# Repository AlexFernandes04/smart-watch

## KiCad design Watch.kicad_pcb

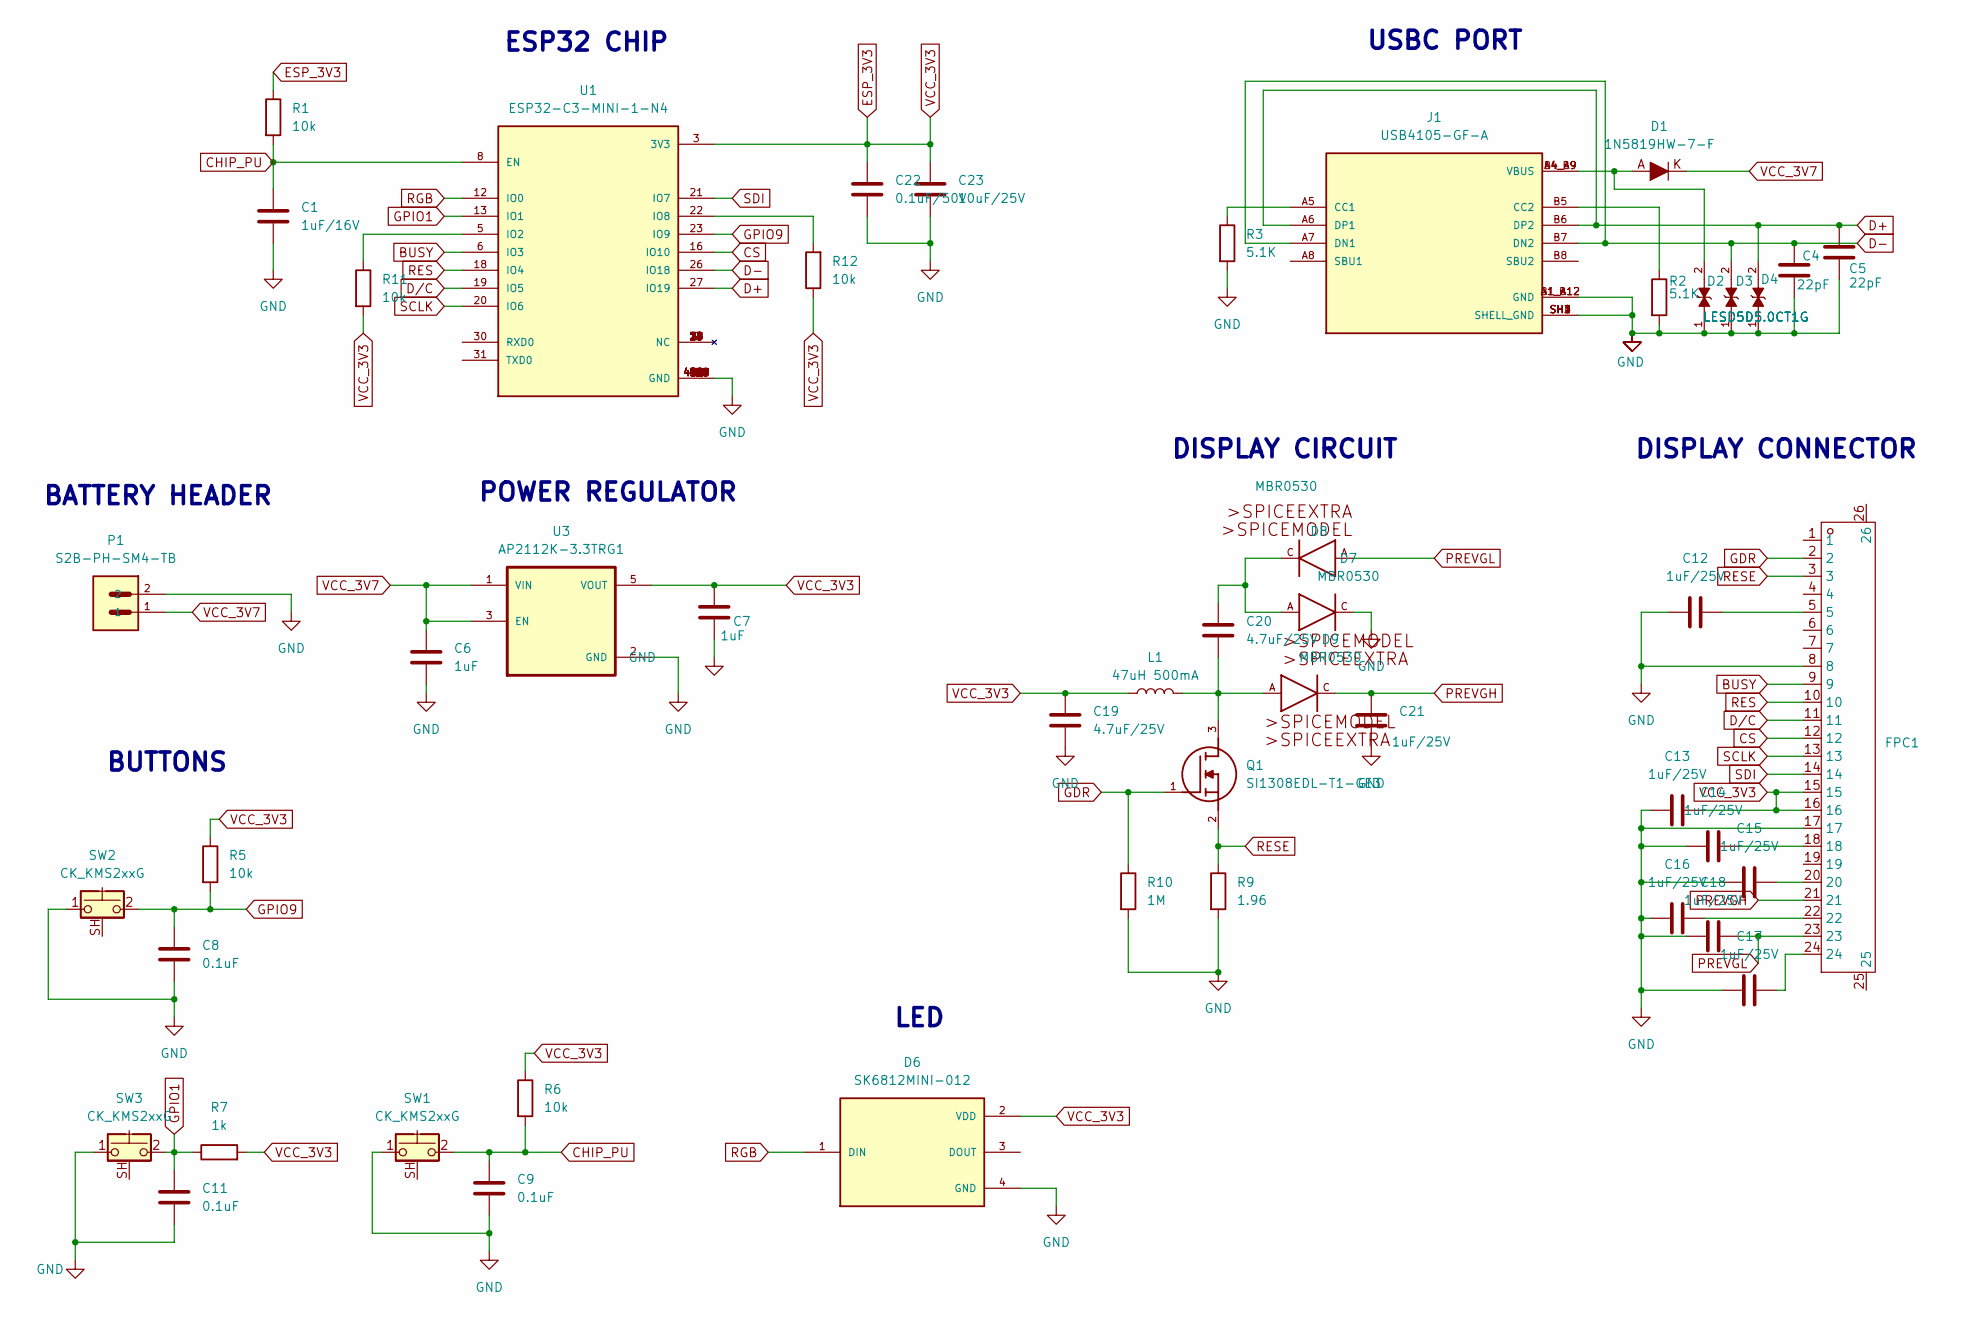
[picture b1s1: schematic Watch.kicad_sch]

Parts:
C1: 1uF/16V; C_0603_1608Metric
C4, C5: 22pF; C_0603_1608Metric
C6, C7: 1uF; C_0603_1608Metric
C8, C9, C11: 0.1uF; C_0603_1608Metric
C12, C13, C14, C15, C16, C17, C18, C21: 1uF/25V; C_0603_1608Metric
C19, C20: 4.7uF/25V; C_0603_1608Metric
C22: 0.1uF/50V; C_0603_1608Metric
C23: 10uF/25V; C_0805_2012Metric
D1: 1N5819HW-7-F; SOD-123; MPN 1N5819HW-7-F; Digi-Key_PN 1N5819HW-FDICT-ND
D2, D3, D4: LESD5D5.0CT1G; TVS_LESD5D5.0CT1G; PARTREV O
D6: SK6812MINI-012; LED_SK6812MINI-012; PARTREV A/0
D7, D8, D9: MBR0530; SOD123
FPC1: FPC-SMD_24P-P0.50_FPC-05F-24PH20; Manufacturer Part FPC-05F-24PH20; LCSC Part Name 间距:0.5mm P数:24P 翻盖式 下接
J1: USB4105-GF-A; GCT_USB4105-GF-A; PARTREV B4
L1: 47uH 500mA; IND-SMD_L7.2-W6.6_GPSR07X0
P1: S2B-PH-SM4-TB; JST_S2B-PH-SM4-TB
Q1: SI1308EDL-T1-GE3; SOT65P210X110-3N; Mouser_Part_Number 78-SI1308EDL-T1-GE3
R1, R5, R6, R11, R12: 10k; R_0603_1608Metric
R2, R3: 5.1K; R_0603_1608Metric
R7: 1k; R_0603_1608Metric
R9: 1.96; R_0603_1608Metric
R10: 1M; R_0603_1608Metric
SW1, SW2, SW3: CK_KMS2xxG; SW_SPST_CK_KMS2xxGP
U1: ESP32-C3-MINI-1-N4; XCVR_ESP32-C3-MINI-1-N4; PARTREV v1.0
U3: AP2112K-3.3TRG1; SOT95P285X140-5N; PARTREV 2-2

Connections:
BUSY: FPC1.9, U1.6 (IO3)
CHIP_PU: C1.1, C9.1, R1.2, R6.2, SW1.2, U1.8 (EN)
CS: FPC1.12, U1.16 (IO10)
D+: C5.1, D4.2, J1.A6 (DP1), J1.B6 (DP2), U1.27 (IO19)
D-: C4.1, D3.2, J1.A7 (DN1), J1.B7 (DN2), U1.26 (IO18)
D/C: FPC1.11, U1.19 (IO5)
ESP_3V3: C7.1, C13.2, C19.1, C22.1, C23.1, D6.2 (VDD), FPC1.15, FPC1.16, L1.1, R1.1, R5.1, R6.1, R7.2, R11.2, R12.1, U1.3 (3V3), U3.5 (VOUT)
GDR: FPC1.2, Q1.1, R10.1
GND: C1.2, C4.2, C5.2, C6.2, C7.2, C8.2, C9.2, C11.2, C12.1, C13.1, C14.1, C15.1, C16.1, C17.1, C18.1, C19.2, C21.2, C22.2, C23.2, D2.1, D3.1, D4.1, D6.4 (GND), D7.C, FPC1.8, FPC1.17, J1.A1_B12 (GND), J1.B1_A12 (GND), J1.SH1 (SHELL_GND), J1.SH2 (SHELL_GND), J1.SH3 (SHELL_GND), J1.SH4 (SHELL_GND), P1.2, R2.2, R3.2, R9.2, R10.2, SW1.1, SW2.1, SW3.1, U1.1 (GND), U1.2 (GND), U1.11 (GND), U1.14 (GND), U1.36 (GND), U1.37 (GND), U1.38 (GND), U1.39 (GND), U1.40 (GND), U1.41 (GND), U1.42 (GND), U1.43 (GND), U1.44 (GND), U1.45 (GND), U1.46 (GND), U1.47 (GND), U1.48 (GND), U1.49_1 (GND), U1.49_2 (GND), U1.49_3 (GND), U1.49_4 (GND), U1.49_5 (GND), U1.49_6 (GND), U1.49_7 (GND), U1.49_8 (GND), U1.49_9 (GND), U1.50 (GND), U1.51 (GND), U1.52 (GND), U1.53 (GND), U3.2 (GND)
GPIO1: C11.1, R7.1, SW3.2, U1.13 (IO1)
GPIO9: C8.1, R5.2, SW2.2, U1.23 (IO9)
unnamed: C12.2, FPC1.5
unnamed: C14.2, FPC1.18
unnamed: C15.2, FPC1.20
unnamed: C16.2, FPC1.22
unnamed: C17.2, FPC1.24
unnamed: C20.1, D7.A, D8.C
unnamed: C20.2, D9.A, L1.2, Q1.3
unnamed: D1.A, D2.2, J1.A4_B9 (VBUS), J1.B4_A9 (VBUS)
unnamed: J1.A5 (CC1), R3.1
unnamed: J1.B5 (CC2), R2.1
unnamed: R11.1, U1.5 (IO2)
unnamed: R12.2, U1.22 (IO8)
PREVGH: C21.1, D9.C, FPC1.21
PREVGL: C18.2, D8.A, FPC1.23
RES: FPC1.10, U1.18 (IO4)
RESE: FPC1.3, Q1.2, R9.1
RGB: D6.1 (DIN), U1.12 (IO0)
SCLK: FPC1.13, U1.20 (IO6)
SDI: FPC1.14, U1.21 (IO7)
VCC_3V7: C6.1, D1.K, P1.1, U3.1 (VIN), U3.3 (EN)

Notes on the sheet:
LED
BUTTONS
DISPLAY CONNECTOR
ESP32 CHIP
DISPLAY CIRCUIT
POWER REGULATOR
BATTERY HEADER
USBC PORT

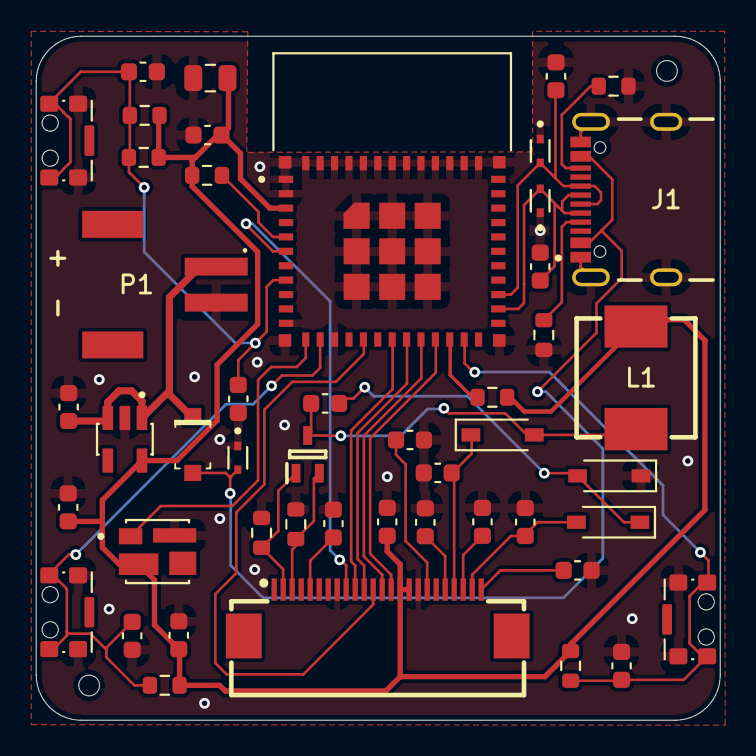
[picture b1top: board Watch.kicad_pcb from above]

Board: 2 copper layers, 38.0 x 38.0 mm, 48 parts (0 on the bottom side), 31 nets.

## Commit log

2025-09-07 Added CAD
2025-09-07 Added Code
2025-09-08 Added PCB files
